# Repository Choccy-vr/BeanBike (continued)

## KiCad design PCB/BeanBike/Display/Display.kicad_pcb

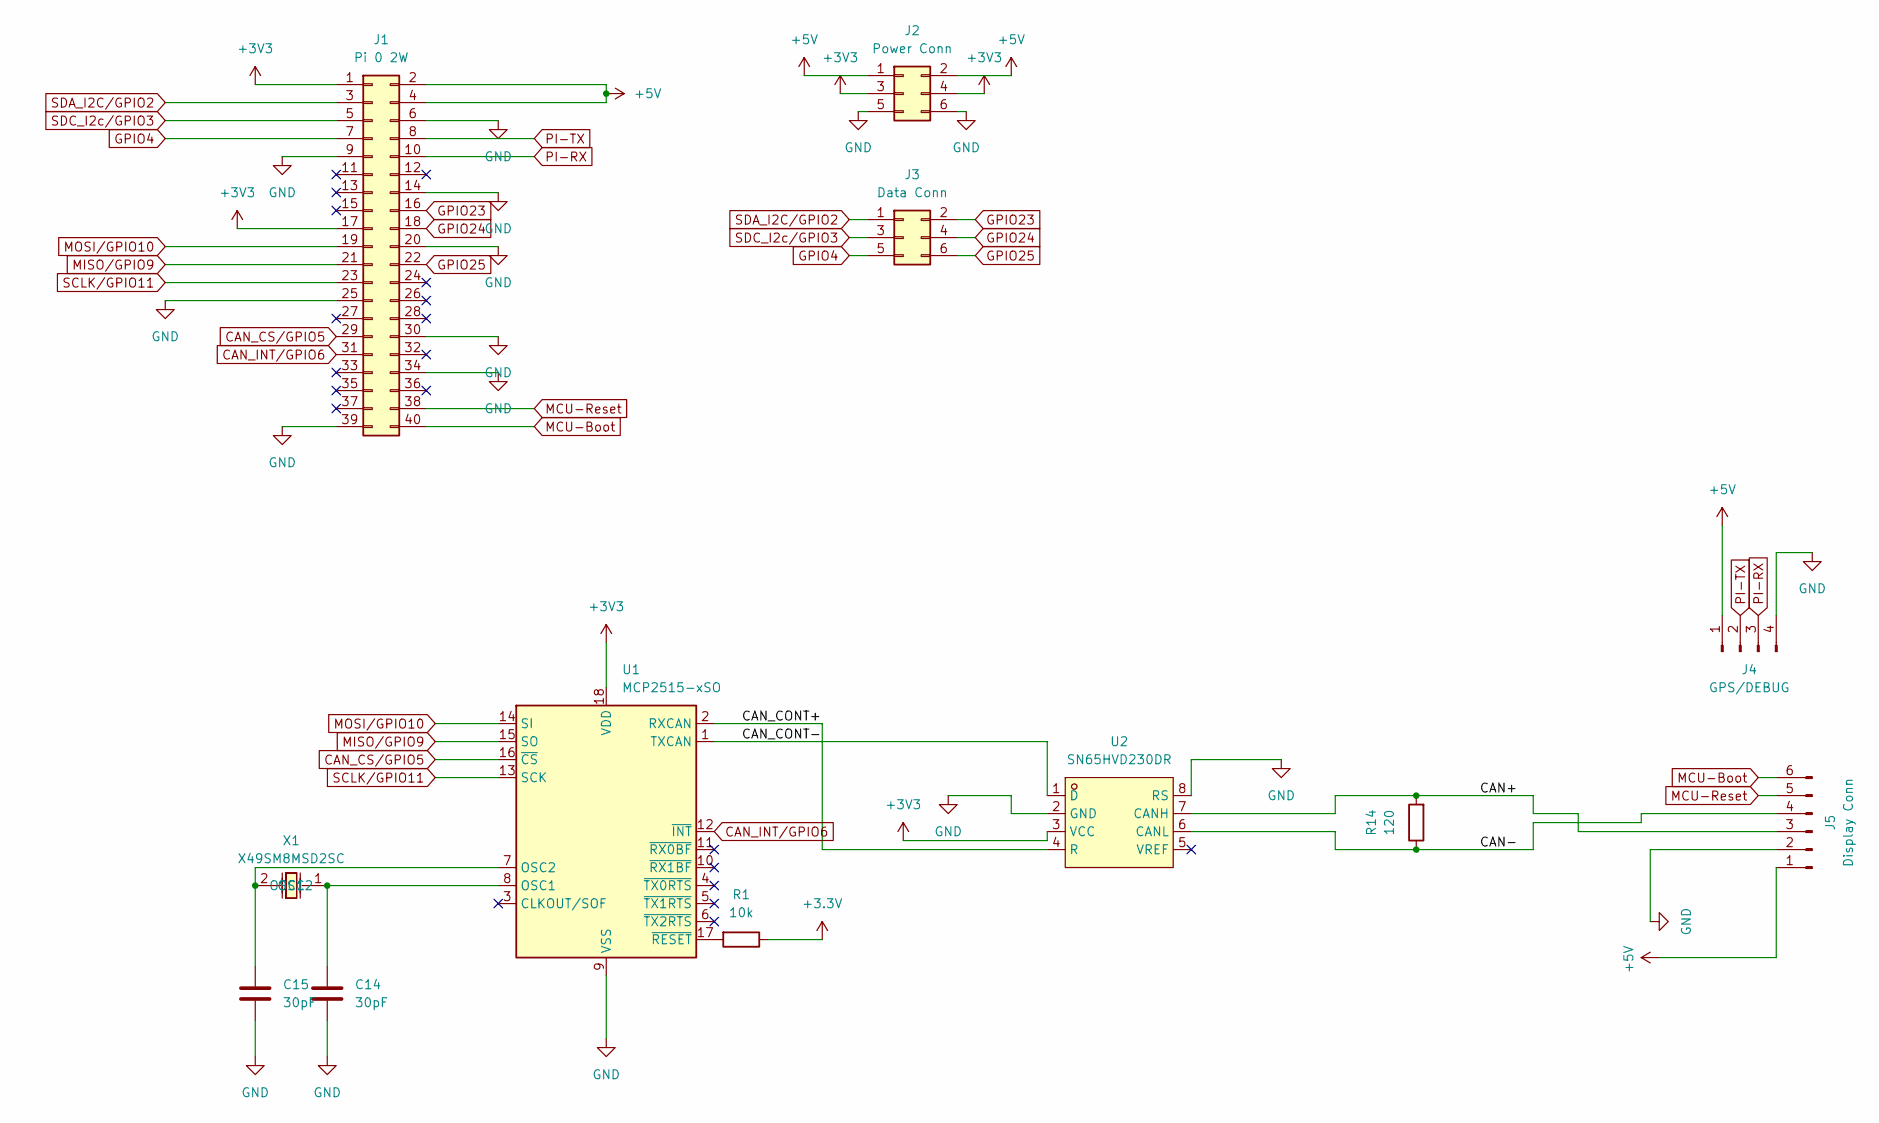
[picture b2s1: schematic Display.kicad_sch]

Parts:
C14, C15: 30pF; C_0402_1005Metric; LCSC C1570
J1: Pi 0 2W; PinSocket_2x20_P2.54mm_Vertical
J2: Power Conn; PinHeader_2x03_P2.54mm_Vertical
J3: Data Conn; PinHeader_2x03_P2.54mm_Vertical
J4: GPS/DEBUG; PinHeader_1x04_P2.54mm_Vertical
J5: Display Conn; PinHeader_1x06_P2.54mm_Vertical
R1: 10k; R_0805_2012Metric; LCSC C17414
R14: 120; R_0805_2012Metric; LCSC C17437
U1: MCP2515-xSO; SOIC-18W_7.5x11.6mm_P1.27mm; LCSC C15193
U2: SN65HVD230DR; SOIC-8_L4.9-W3.9-P1.27-LS6.0-BL; LCSC Part C12084
X1: X49SM8MSD2SC; CRYSTAL-SMD_L11.5-W4.8-LS12.7; LCSC Part C12674

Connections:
+3.3V: R1.1
+3V3: J1.1, J1.17, J2.3, J2.4, U1.18 (VDD), U2.3 (VCC)
+5V: J1.2, J1.4, J2.1, J2.2, J4.1, J5.1
/CAN+: J5.3, R14.2, U2.7 (CANH)
/CAN-: J5.4, R14.1, U2.6 (CANL)
/CAN_CONT+: U1.2 (RXCAN), U2.4 (R)
/CAN_CONT-: U1.1 (TXCAN), U2.1 (D)
CAN_CS/GPIO5: J1.29, U1.16 (~CS)
CAN_INT/GPIO6: J1.31, U1.12 (~INT)
GND: C14.2, C15.2, J1.6, J1.9, J1.14, J1.20, J1.25, J1.30, J1.34, J1.39, J2.5, J2.6, J4.4, J5.2, U1.9 (VSS), U2.2 (GND), U2.8 (RS)
GPIO4: J1.7, J3.5
GPIO23: J1.16, J3.2
GPIO24: J1.18, J3.4
GPIO25: J1.22, J3.6
MCU-Boot: J1.40, J5.6
MCU-Reset: J1.38, J5.5
MISO/GPIO9: J1.21, U1.15 (SO)
MOSI/GPIO10: J1.19, U1.14 (SI)
unnamed: C14.1, U1.8 (OSC1), X1.1 (OSC1)
unnamed: C15.1, U1.7 (OSC2), X1.2 (OSC2)
unnamed: R1.2, U1.17 (~RESET)
PI-RX: J1.10, J4.3
PI-TX: J1.8, J4.2
SCLK/GPIO11: J1.23, U1.13 (SCK)
SDA_I2C/GPIO2: J1.3, J3.1
SDC_I2c/GPIO3: J1.5, J3.3

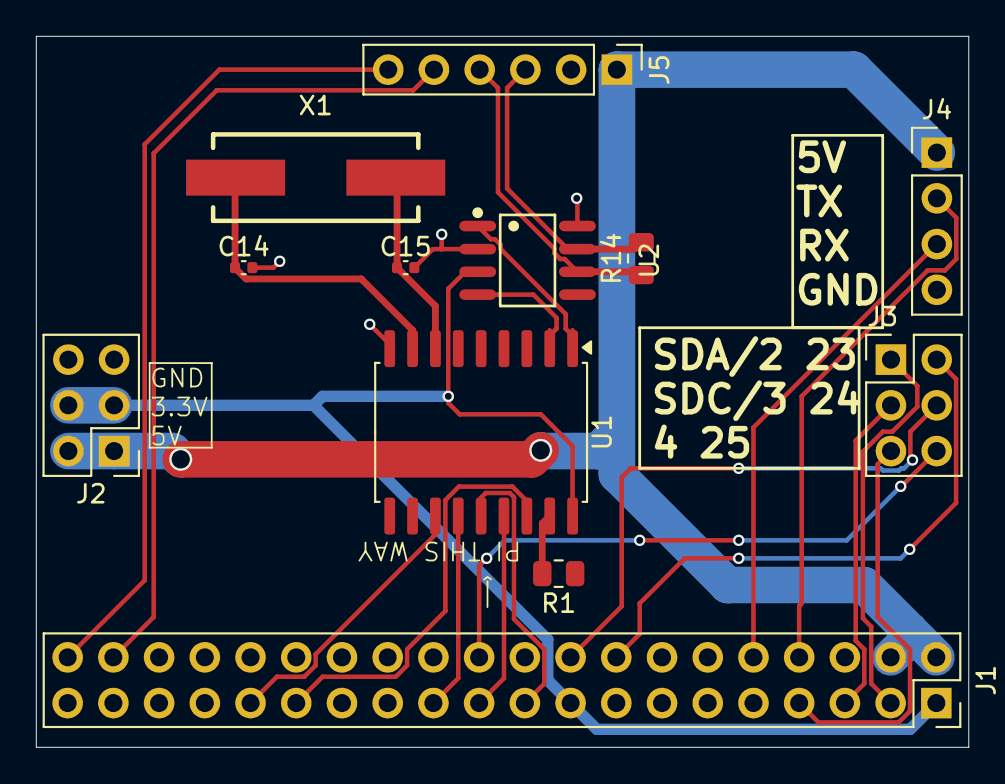
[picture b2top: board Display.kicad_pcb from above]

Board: 2 copper layers, 51.8 x 39.5 mm, 12 parts (0 on the bottom side), 25 nets.

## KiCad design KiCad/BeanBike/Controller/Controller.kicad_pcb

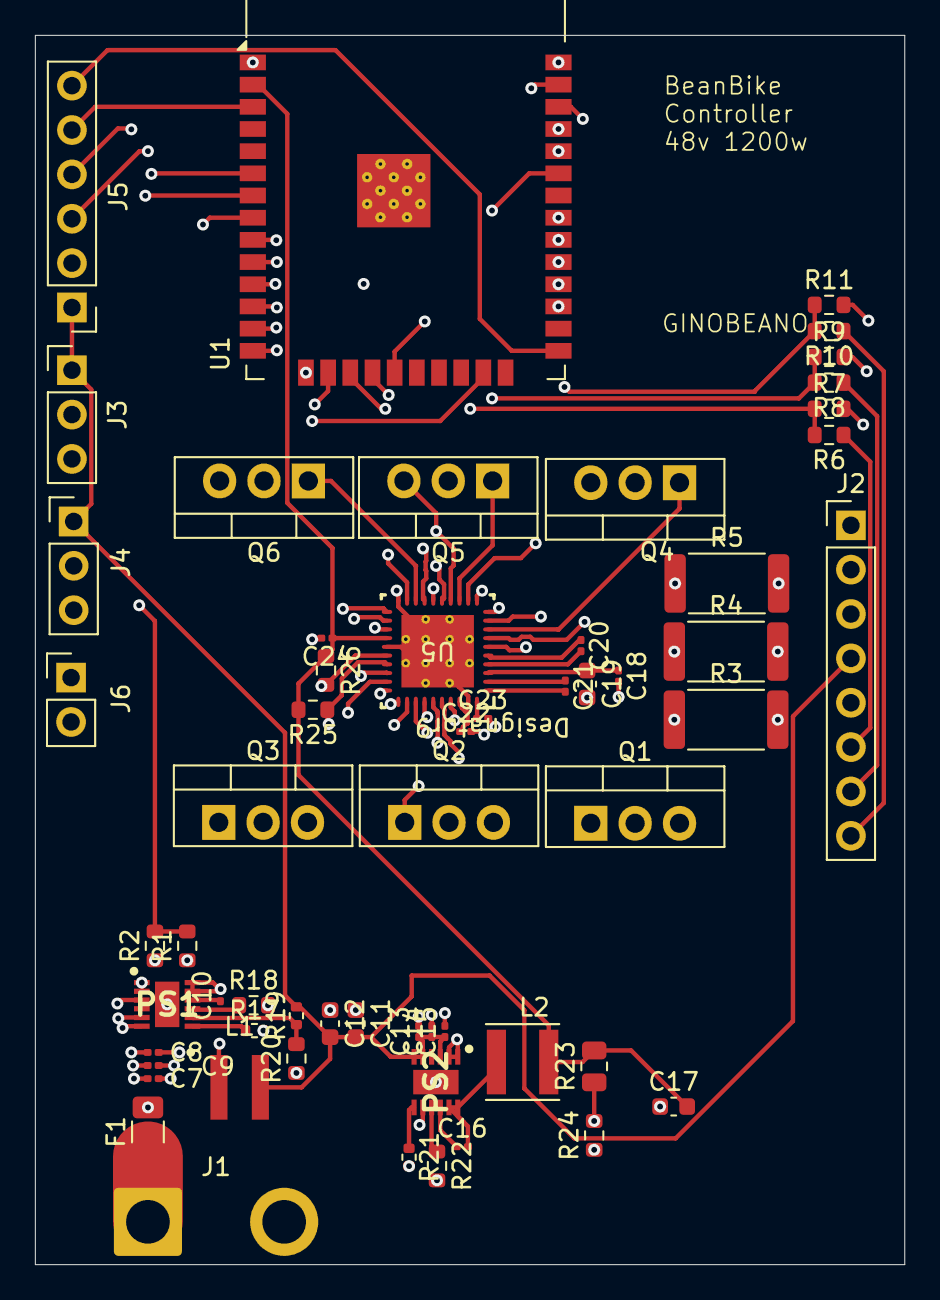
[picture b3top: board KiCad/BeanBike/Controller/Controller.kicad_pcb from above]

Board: 6 copper layers, 49.8 x 70.4 mm, 58 parts (0 on the bottom side), 60 nets.

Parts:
C7, C8, C13, C14: 2.2uF; C_0201_0603Metric
C9, C15: 100nF; C_0201_0603Metric
C10, C16: 100nf; C_0201_0603Metric
C11, C12, C17: 22uF; C_0603_1608Metric
C18, C24: 0.1uF; C_0201_0603Metric
C19: >10uF; C_0603_1608Metric
C20, C22, C23: 1uF; C_0201_0603Metric
C21: 47nF; C_0201_0603Metric
F1: Fuse; Fuse_1206_3216Metric
J1: XT80 Male; SolderWire-2sqmm_1x02_P7.8mm_D2mm_OD3.9mm
J2: Motor Conn; PinHeader_1x08_P2.54mm_Vertical
J3: Throttle Conn; PinHeader_1x03_P2.54mm_Vertical
J4: PAS Conn; PinHeader_1x03_P2.54mm_Vertical
J5: Display Conn; PinHeader_1x06_P2.54mm_Vertical
J6: Brake Conn; PinHeader_1x02_P2.54mm_Vertical
L1: 8.2uH 68mOhm; WE-MAPI_4030
L2: L; IND_PA4332.152NLT
PS1, PS2: LMR38025SQDRRRQ1; SON50P300X300X80-13N
Q1: PHASE A HIGH; TO-220-3_Vertical
Q2: PHASE B HIGH; TO-220-3_Vertical
Q3: PHASE C HIGH; TO-220-3_Vertical
Q4: PHASE A LOW; TO-220-3_Vertical
Q5: PHASE B LOW; TO-220-3_Vertical
Q6: PHASE C LOW; TO-220-3_Vertical
R1, R6, R8, R10, R18, R20, R22, R24: 10k; R_0603_1608Metric
R2: 180k; R_0603_1608Metric
R3, R4, R5: CSS2H-2512R-1L00F; R_2512_6332Metric
R7, R9, R11: 18k; R_0603_1608Metric
R17: 46.4k; R_0402_1005Metric
R19: 40.2k; R_0402_1005Metric
R21: 21.5k; R_0402_1005Metric
R23: 23.2k; R_0805_2012Metric
R25, R26: 73k; R_0603_1608Metric
U1: ESP32-WROOM-32
U5: DRV8353SRTAT; RTA0040B

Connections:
+3.3V: C17.2, C24.1, L2.2, R23.2, R25.2, R26.1, U1.2 (VDD), U5.24 (VREF)
+BATT: F1.1, J1.1
/Motor/VDRAIN: C20.2, U5.4 (VDRAIN)
BATT_Level: R1.2, R2.2, U1.27 (IO16)
BLDC-IC_PHASE_A_HIGH: Q1.1 (G), U5.6 (GHA)
BLDC-IC_PHASE_A_LOW: Q4.1 (G), U5.8 (GLA)
BLDC-IC_PHASE_B_HIGH: Q2.1 (G), U5.15 (GHB)
BLDC-IC_PHASE_B_LOW: Q5.1 (G), U5.13 (GLB)
BLDC-IC_PHASE_C_HIGH: Q3.1 (G), U5.16 (GHC)
BLDC-IC_PHASE_C_LOW: Q6.1 (G), U5.18 (GLC)
BRAKE_GND: C7.2, C8.2, C9.2, C11.1, C12.1, C13.2, C14.2, C15.2, C17.1, C18.2, C19.2, C22.2, C23.2, C24.2, J1.2, J2.5, J3.2, J4.2, J5.2, J6.1, PS1.1 (GND_1), PS1.2 (GND_2), PS1.13 (EP), PS2.1 (GND_1), PS2.2 (GND_2), PS2.13 (EP), Q4.2 (D), Q5.2 (D), Q6.2 (D), R1.1, R3.2, R4.2, R5.2, R7.2, R9.2, R11.2, R17.2, R18.2, R20.1, R21.2, R22.2, R24.1, U1.1 (GND), U1.15 (GND), U1.38 (GND), U1.39 (GND), U5.10 (SNA), U5.11 (SNB), U5.20 (SNC), U5.25 (AGND), U5.39 (PGND), U5.41 (PAD)
BRAKE_SIGNAL: J6.2, U1.8 (IO32)
DISPLAY_5V: C11.2, C12.2, C13.1, C14.1, C15.1, J2.4, J3.1, J4.1, J5.1, L1.2, PS2.3 (EN), PS2.5 (VIN_1), PS2.6 (VIN_2), R19.2
MCU-Boot: J5.6, U1.25 (IO0)
MCU-GPIO5: U1.29 (IO5), U5.30 (SCS_N)
MCU-GPIO9: R6.2, R7.1, U1.17 (SHD/SD2)
MCU-GPIO10: R8.2, R9.1, U1.18 (SWP/SD3)
MCU-GPIO11: R10.2, R11.1, U1.19 (SCS/CMD)
MCU-GPIO12: U1.14 (IO12), U5.32 (INHA)
MCU-GPIO13: U1.16 (IO13), U5.31 (ENABLE)
MCU-GPIO14: U1.13 (IO14), U5.33 (INLA)
MCU-GPIO15: R26.2, U1.23 (IO15), U5.26 (FAULT_N)
MCU-GPIO17: U1.28 (IO17), U5.21 (SOC)
MCU-GPIO18: U1.30 (IO18), U5.29 (SCLK)
MCU-GPIO19: R25.1, U1.31 (IO19), U5.27 (SDO)
MCU-GPIO21: U1.33 (IO21), U5.23 (SOA)
MCU-GPIO22: U1.36 (IO22), U5.22 (SOB)
MCU-GPIO23: U1.37 (IO23), U5.28 (SDI)
MCU-GPIO25: U1.10 (IO25), U5.36 (INHC)
MCU-GPIO26: U1.11 (IO26), U5.35 (INLB)
MCU-GPIO27: U1.12 (IO27), U5.34 (INHB)
MCU-GPIO33: U1.9 (IO33), U5.37 (INLC)
MCU-GPIO34: J3.3, U1.6 (IO34)
MCU-GPIO35: J4.3, U1.7 (IO35)
MCU-RX: J5.3, U1.34 (RXD0/IO3)
MCU-Reset: J5.5, U1.3 (EN)
MCU-TX: J5.4, U1.35 (TXD0/IO1)
MOTOR_HALL_A: J2.6, R6.1
MOTOR_HALL_B: J2.7, R8.1
MOTOR_HALL_C: J2.8, R10.1
MOTOR_PHASE_A: J2.1, Q1.3 (S), Q4.3 (S), R5.1, U5.7 (SHA), U5.9 (SPA)
MOTOR_PHASE_B: J2.2, Q2.3 (S), Q5.3 (S), R4.1, U5.12 (SPB), U5.14 (SHB)
MOTOR_PHASE_C: J2.3, Q3.3 (S), Q6.3 (S), R3.1, U5.17 (SHC), U5.19 (SPC)
unnamed: C10.1, PS1.10 (BOOT)
unnamed: PS1.8 (FB), R19.1, R20.2
unnamed: PS1.9 (PG), R18.1
unnamed: PS1.7 (RT/SYNC), R17.1
unnamed: C10.2, L1.1, PS1.11 (SW_1), PS1.12 (SW_2)
unnamed: C16.1, PS2.10 (BOOT)
unnamed: PS2.8 (FB), R23.1, R24.2
unnamed: PS2.9 (PG), R22.1
unnamed: PS2.7 (RT/SYNC), R21.1
unnamed: C16.2, L2.1, PS2.11 (SW_1), PS2.12 (SW_2)
unnamed: C21.1, U5.2 (CPH)
unnamed: C21.2, U5.1 (CPL)
unnamed: C22.1, U5.38 (DVDD)
unnamed: C20.1, U5.5 (VCP)
unnamed: C23.1, U5.40 (VGLS)
unnamed: C18.1, C19.1, U5.3 (VM)
PWR_MOTOR: C7.1, C8.1, C9.1, F1.2, PS1.3 (EN), PS1.5 (VIN_1), PS1.6 (VIN_2), Q1.2 (D), Q2.2 (D), Q3.2 (D), R2.1

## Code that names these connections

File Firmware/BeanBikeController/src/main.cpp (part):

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#include <SPI.h>

// DRV8353S SPI + control pins
const int DRV_CS_PIN     = PA4;   // SPI CS
const int DRV_ENABLE_PIN = PC9;   // nSLEEP / ENABLE
const int DRV_FAULT_PIN  = PC8;   // nFAULT (active low)

// Motor driver pins (6-PWM)
const int PWM_PIN_AH = PA8;       // Phase A High
const int PWM_PIN_AL = PB13;      // Phase A Low
const int PWM_PIN_BH = PA9;       // Phase B High
const int PWM_PIN_BL = PB14;      // Phase B Low
const int PWM_PIN_CH = PA10;      // Phase C High
const int PWM_PIN_CL = PB15;      // Phase C Low

// Current sense inputs (not used here, keep as inputs)
const int SOA_PIN = PA0;
const int SOB_PIN = PA1;
const int SOC_PIN = PA2;

// Status LED
const int LED_PIN = PB5;

// SPI pins (STM32 default SPI1)
const int SPI_MOSI = PA7;  // SPI1_MOSI
const int SPI_MISO = PA6;  // SPI1_MISO
const int SPI_SCK  = PA5;  // SPI1_SCK

// DRV8353S register addresses
#define DRV8353_FAULT_STATUS_1 0x00
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  if (received == 0xFF) {
    Serial.println("  ⚠️  MISO is stuck HIGH - not responding to clock!");
    Serial.println("  This confirms hardware issue:");
    Serial.println("    - DRV8353 SDO pin not connected to PA6, OR");
    Serial.println("    - DRV8353 PVDD not powered, OR");
    Serial.println("    - Wrong DRV8353 variant (M series has no SPI)");
  } else if (received == 0x00) {
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  digitalWrite(PWM_PIN_CH, LOW);
  digitalWrite(PWM_PIN_CL, LOW);
  
  Serial.println("  CS Pin:     PA4 (HIGH)");
  Serial.println("  Enable Pin: PC9 (LOW - disabled)");
  Serial.println("  Fault Pin:  PC8 (INPUT)");
  Serial.println("  LED Pin:    PB5 (OUTPUT)");
  Serial.println("  SPI MOSI:   PA7");
  Serial.println("  SPI MISO:   PA6");
  Serial.println("  SPI SCK:    PA5");
  
  // Initialize SPI
  Serial.println("\nInitializing SPI...");
  Serial.println("  Default SPI1 Pins:");
  Serial.println("    MOSI: PA7 (SPI1_MOSI)");
  Serial.println("    MISO: PA6 (SPI1_MISO)");
  Serial.println("    SCK:  PA5 (SPI1_SCK)");
  Serial.println("    CS:   PA4 (Manual)");
  
  SPI.begin();
  Serial.println("  SPI Mode: 1 (CPOL=0, CPHA=1)");
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    Serial.println("     - VM/VDRAIN (motor power supply) connected?");
    Serial.println("     - All GND pins connected?");
    Serial.println("  2. SPI connections:");
    Serial.println("     - STM32 PA6 (MISO) → DRV8353 SDO pin");
    Serial.println("     - STM32 PA7 (MOSI) → DRV8353 SDI pin");
    Serial.println("     - STM32 PA5 (SCK)  → DRV8353 SCLK pin");
    Serial.println("     - STM32 PA4 (CS)   → DRV8353 nSCS pin");
    Serial.println("  3. DRV8353 variant:");
    Serial.println("     - DRV8353S/RS/RH: Has SPI interface");
    Serial.println("     - DRV8353M: Hardware control only (no SPI!)");
    Serial.println("  4. Mode selection pins (if present):");
    Serial.println("     - Some DRV8353 variants need SPI_EN or MODE pins configured");
    Serial.println("  5. Enable pin:");
    Serial.println("     - nSLEEP/ENABLE (PC9) should be HIGH during SPI communication");
    Serial.println("================================================\n");
  } else if (test1 == 0x00 && test2 == 0x00) {
    Serial.println("  ⚠️  WARNING: MISO stuck LOW - check wiring!");
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  
  // Add pin state monitoring
  Serial.println("\n========== Pin State Monitoring ==========");
  Serial.print("  DRV_ENABLE (PC9): ");
  Serial.println(digitalRead(DRV_ENABLE_PIN) ? "HIGH" : "LOW");
  Serial.print("  DRV_FAULT (PC8):  ");
  Serial.println(digitalRead(DRV_FAULT_PIN) ? "HIGH (OK)" : "LOW (FAULT!)");
  Serial.print("  SPI_MISO (PA6):   ");
  Serial.println(digitalRead(SPI_MISO) ? "HIGH" : "LOW");
  Serial.println("==========================================\n");
  
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
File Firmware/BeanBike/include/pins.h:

#ifndef PINS_H
#define PINS_H

#include <stdint.h>

struct PinDef {
    const char* name;
    int pin;
    uint8_t mode;
};

class Pins {
public:
    // Pins
    static const PinDef BATT_LEVEL;
    static const PinDef MOTOR_ENABLE;
    static const PinDef MOTOR_INHA;
    static const PinDef MOTOR_INLA;
    static const PinDef MOTOR_INHB;  
    static const PinDef MOTOR_INLB;
    static const PinDef MOTOR_INHC;
    static const PinDef MOTOR_INLC;
    static const PinDef MOTOR_SOA;
    static const PinDef MOTOR_SOB;
    static const PinDef MOTOR_SOC;
    static const PinDef MOTOR_HALL_A;
    static const PinDef MOTOR_HALL_B;
    static const PinDef MOTOR_HALL_C;
    static const PinDef MOTOR_FAULT;
    static const PinDef SENSOR_THROTTLE_DATA;
    static const PinDef SENSOR_PAS_PULSE;
    static const PinDef SENSOR_BRAKE_SIGNAL;

    // Functions
    void initPins();
};

#endif

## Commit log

2025-10-10 Init Commit
    Just setup a KiCad project
2025-10-11 Power Circuit V1
2025-10-11 Connectors
2025-10-13 PCB v1
    Whole lotta stuff
2025-10-15 PCB v2
2025-10-19 PCBv2 Finish
2025-10-19 Silkscreen
2025-10-21 More Firmware
    😄
2025-10-21 FIRMWARE v1
2025-10-26 Finishing Things Up
2025-10-26 Finishing touches/Shipping
2025-10-26 Rename BeanBike-BOM.csv to bom.csv
2025-11-03 Forgot to commit
2025-11-05 STM32
2025-11-05 Fix Spacing and Layout
2025-11-07 Schematic v3 Done
2025-11-08 Footprints
2025-11-08 PCB v3
2025-11-09 Fix grammar and update BOM formatting in README
    Corrected grammar and punctuation in the README file, particularly in the 'Why?' section. Updated the BOM table formatting and content.
2025-11-09 Finish up
2025-12-28 big ol update
